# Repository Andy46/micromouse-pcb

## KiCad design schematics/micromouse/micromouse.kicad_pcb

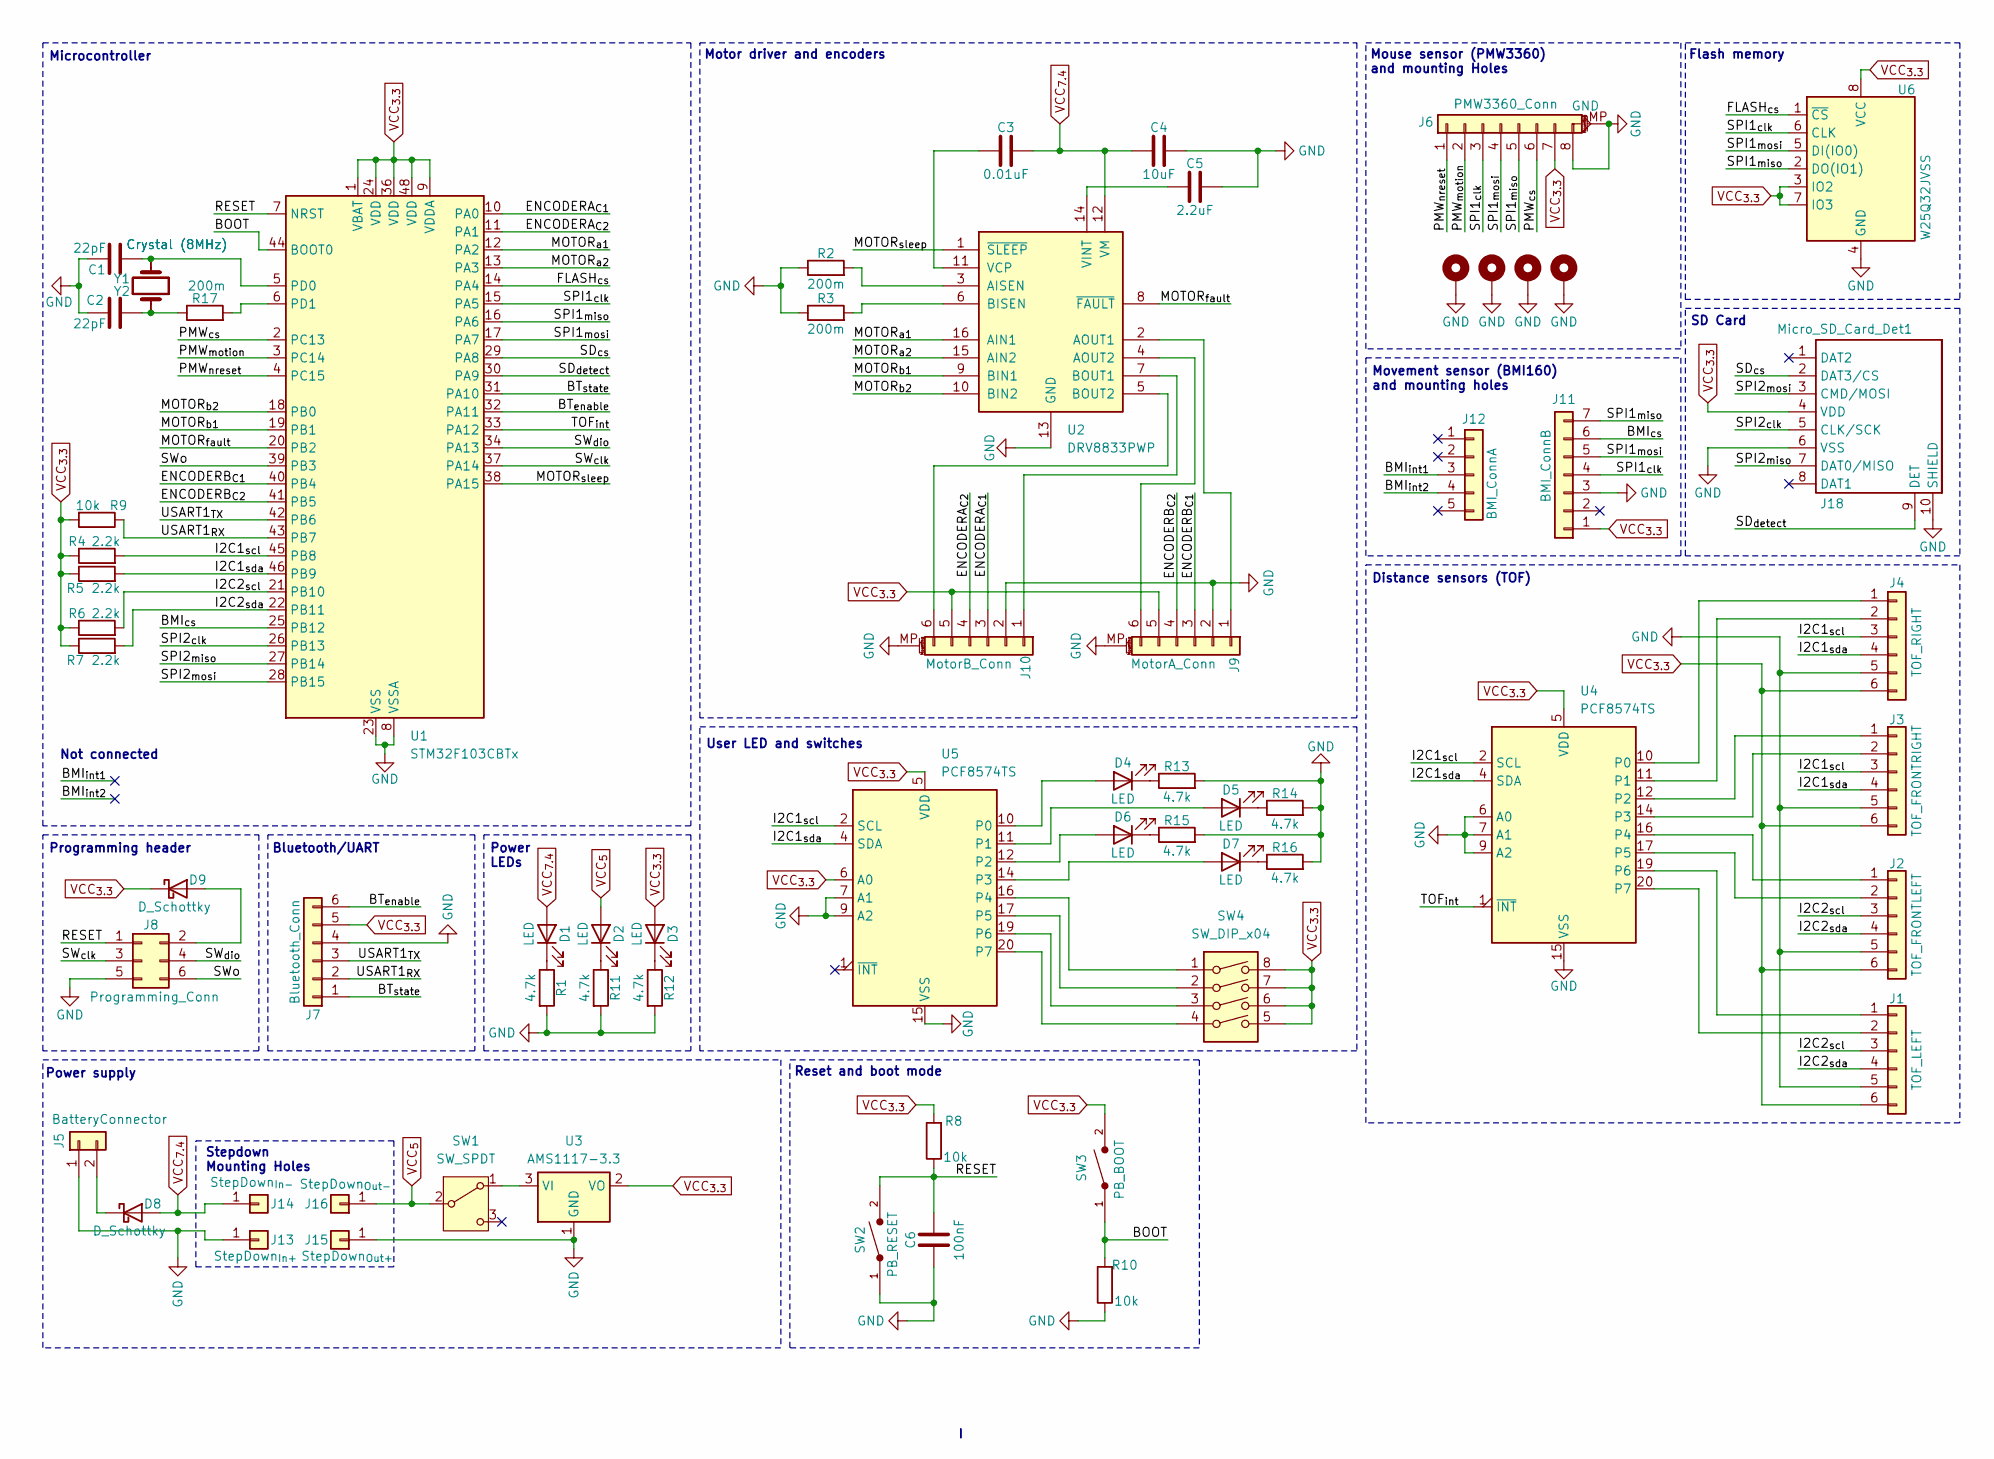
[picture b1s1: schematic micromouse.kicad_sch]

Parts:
C1, C2: 22pF; C_0805_2012Metric_Pad1.18x1.45mm_HandSolder
C3: 0.01uF; C_0805_2012Metric_Pad1.18x1.45mm_HandSolder
C4: 10uF; C_0805_2012Metric_Pad1.18x1.45mm_HandSolder
C5: 2.2uF; C_0805_2012Metric_Pad1.18x1.45mm_HandSolder
C6: 100nF; C_0805_2012Metric_Pad1.18x1.45mm_HandSolder
D1, D2, D3, D4, D5, D6, D7: LED; LED_0805_2012Metric_Pad1.15x1.40mm_HandSolder
D8, D9: D_Schottky; D_SOD-123
H1, H2, H3, H4: MountingHole_Pad; MountingHole_2.2mm_M2_ISO14580_Pad
J1: TOF_LEFT; PinHeader_1x06_P2.54mm_Vertical
J2: TOF_FRONTLEFT; PinHeader_1x06_P2.54mm_Vertical
J3: TOF_FRONTRIGHT; PinHeader_1x06_P2.54mm_Vertical
J4: TOF_RIGHT; PinHeader_1x06_P2.54mm_Vertical
J5: BatteryConnector; JST_XH_B2B-XH-A_1x02_P2.50mm_Vertical
J6: PMW3360_Conn; JST_SH_BM08B-SRSS-TB_1x08-1MP_P1.00mm_Vertical
J7: Bluetooth_Conn; PinHeader_1x06_P2.54mm_Vertical
J8: Programming_Conn; PinHeader_2x03_P2.54mm_Vertical
J9: MotorA_Conn; JST_SH_BM06B-SRSS-TB_1x06-1MP_P1.00mm_Vertical
J10: MotorB_Conn; JST_SH_BM06B-SRSS-TB_1x06-1MP_P1.00mm_Vertical
J11: BMI_ConnB; PinHeader_1x07_P2.54mm_Vertical
J12: BMI_ConnA; PinHeader_1x05_P2.54mm_Vertical
J13: StepDown_{In+}; PinHeader_1x01_P2.54mm_Vertical
J14: StepDown_{In-}; PinHeader_1x01_P2.54mm_Vertical
J15: StepDown_{Out+}; PinHeader_1x01_P2.54mm_Vertical
J16: StepDown_{Out-}; PinHeader_1x01_P2.54mm_Vertical
J18: Micro_SD_Card_Det1; microSD_HC_Hirose_DM3D-SF
R1, R11, R12, R13, R14, R15, R16: 4.7k; R_0805_2012Metric_Pad1.20x1.40mm_HandSolder
R2, R3, R17: 200m; R_0805_2012Metric_Pad1.20x1.40mm_HandSolder
R4, R5, R6, R7: 2.2k; R_0805_2012Metric_Pad1.20x1.40mm_HandSolder
R8, R9, R10: 10k; R_0805_2012Metric_Pad1.20x1.40mm_HandSolder
SW1: SW_SPDT; SW_SPDT_PCM12
SW2: PB_RESET; TE_FSMSM; PARTREV C2
SW3: PB_BOOT; TE_FSMSM; PARTREV C2
SW4: SW_DIP_x04; SW_DIP_SPSTx04_Slide_9.78x12.34mm_W7.62mm_P2.54mm
U1: STM32F103CBTx; LQFP-48_7x7mm_P0.5mm
U2: DRV8833PWP; HTSSOP-16-1EP_4.4x5mm_P0.65mm_EP3.4x5mm_Mask2.46x2.31mm_The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
U3: AMS1117-3.3; SOT-223-3_TabPin2
U4, U5: PCF8574TS; SSOP-20_4.4x6.5mm_P0.65mm
U6: W25Q32JVSS; SOIC-8_5.23x5.23mm_P1.27mm
Y1: Crystal (8MHz); Crystal_SMD_HC49-SD
Y2: Crystal (8MHz); Crystal_HC49-4H_Vertical

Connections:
/BMI_{cs}: J11.6, U1.25 (PB12)
/BMI_{int1}: J12.3
/BMI_{int2}: J12.4
/BOOT: R10.2, SW3.1, U1.44 (BOOT0)
/BT_{enable}: J7.6, U1.32 (PA11)
/BT_{state}: J7.1, U1.31 (PA10)
/ENCODERA_{C1}: J10.3, U1.10 (PA0)
/ENCODERA_{C2}: J10.4, U1.11 (PA1)
/ENCODERB_{C1}: J9.3, U1.40 (PB4)
/ENCODERB_{C2}: J9.4, U1.41 (PB5)
/FLASH_{cs}: U1.14 (PA4), U6.1 (~CS)
/I2C1_{scl}: J3.3, J4.3, R4.2, U1.45 (PB8), U4.2 (SCL), U5.2 (SCL)
/I2C1_{sda}: J3.4, J4.4, R5.2, U1.46 (PB9), U4.4 (SDA), U5.4 (SDA)
/I2C2_{scl}: J1.3, J2.3, R6.2, U1.21 (PB10)
/I2C2_{sda}: J1.4, J2.4, R7.2, U1.22 (PB11)
/MOTOR_{a1}: U1.12 (PA2), U2.16 (AIN1)
/MOTOR_{a2}: U1.13 (PA3), U2.15 (AIN2)
/MOTOR_{b1}: U1.19 (PB1), U2.9 (BIN1)
/MOTOR_{b2}: U1.18 (PB0), U2.10 (BIN2)
/MOTOR_{fault}: U1.20 (PB2), U2.8 (~FAULT)
/MOTOR_{sleep}: U1.38 (PA15), U2.1 (~SLEEP)
/PMW_{cs}: J6.6, U1.2 (PC13)
/PMW_{motion}: J6.2, U1.3 (PC14)
/PMW_{nreset}: J6.1, U1.4 (PC15)
/RESET: C6.1, J8.1, R8.1, SW2.2, U1.7 (NRST)
/SD_{cs}: J18.2 (DAT3/CS), U1.29 (PA8)
/SD_{detect}: J18.9 (DET), U1.30 (PA9)
/SPI1_{clk}: J6.3, J11.4, U1.15 (PA5), U6.6 (CLK)
/SPI1_{miso}: J6.5, J11.7, U1.16 (PA6), U6.2 (DO(IO1))
/SPI1_{mosi}: J6.4, J11.5, U1.17 (PA7), U6.5 (DI(IO0))
/SPI2_{clk}: J18.5 (CLK/SCK), U1.26 (PB13)
/SPI2_{miso}: J18.7 (DAT0/MISO), U1.27 (PB14)
/SPI2_{mosi}: J18.3 (CMD/MOSI), U1.28 (PB15)
/SW_{clk}: J8.3, U1.37 (PA14)
/SW_{dio}: J8.4, U1.34 (PA13)
/SWo: J8.6, U1.39 (PB3)
/TOF_{int}: U1.33 (PA12), U4.1 (~INT)
/USART1_{RX}: J7.2, R9.1, U1.43 (PB7)
/USART1_{TX}: J7.3, U1.42 (PB6)
GND: C1.1, C2.2, C4.2, C5.2, C6.2, H1.1, H2.1, H3.1, H4.1, J1.5, J2.5, J3.5, J4.5, J5.1, J6.8, J6.MP (MountPin), J7.4, J8.5, J9.2, J9.MP (MountPin), J10.2, J10.MP (MountPin), J11.3, J13.1, J15.1, J18.6 (VSS), J18.10 (SHIELD), R1.2, R2.1, R3.1, R10.1, R11.2, R12.2, R13.2, R14.2, R15.2, R16.2, SW2.1, U1.8 (VSSA), U1.23 (VSS), U1.35 (VSS), U1.47 (VSS), U2.13 (GND), U2.17 (GND), U3.1 (GND), U4.6 (A0), U4.7 (A1), U4.9 (A2), U4.15 (VSS), U5.7 (A1), U5.9 (A2), U5.15 (VSS), U6.4 (GND)
unnamed: C2.1, R17.1, Y1.1, Y2.1
unnamed: D1.1 (K), R1.1
unnamed: D2.1 (K), R11.1
unnamed: D3.1 (K), R12.1
unnamed: D4.2 (A), U5.10 (P0)
unnamed: D4.1 (K), R13.1
unnamed: D5.2 (A), U5.11 (P1)
unnamed: D5.1 (K), R14.1
unnamed: D6.2 (A), U5.12 (P2)
unnamed: D6.1 (K), R15.1
unnamed: D7.2 (A), U5.14 (P3)
unnamed: D7.1 (K), R16.1
unnamed: D8.1 (K), J5.2
unnamed: D9.2 (A), J8.2
unnamed: J1.1, U4.19 (P6)
unnamed: J1.2, U4.20 (P7)
unnamed: J2.1, U4.16 (P4)
unnamed: J2.2, U4.17 (P5)
unnamed: J3.1, U4.12 (P2)
unnamed: J3.2, U4.14 (P3)
unnamed: J4.1, U4.10 (P0)
unnamed: J4.2, U4.11 (P1)
unnamed: J9.1, U2.2 (AOUT1)
unnamed: J9.6, U2.4 (AOUT2)
unnamed: J10.1, U2.7 (BOUT1)
unnamed: J10.6, U2.5 (BOUT2)
unnamed: SW1.1 (A), U3.3 (VI)
unnamed: C1.2, U1.5 (PD0), Y1.2, Y2.2
unnamed: R17.2, U1.6 (PD1)
unnamed: R2.2, U2.3 (AISEN)
unnamed: R3.2, U2.6 (BISEN)
unnamed: C3.1, U2.11 (VCP)
unnamed: C5.1, U2.14 (VINT)
unnamed: SW4.1, U5.16 (P4)
unnamed: SW4.2, U5.17 (P5)
unnamed: SW4.3, U5.19 (P6)
unnamed: SW4.4, U5.20 (P7)
VCC_{3.3}: D3.2 (A), D9.1 (K), J1.6, J2.6, J3.6, J4.6, J6.7, J7.5, J9.5, J10.5, J11.1, J18.4 (VDD), R4.1, R5.1, R6.1, R7.1, R8.2, R9.2, SW3.2, SW4.5, SW4.6, SW4.7, SW4.8, U1.1 (VBAT), U1.9 (VDDA), U1.24 (VDD), U1.36 (VDD), U1.48 (VDD), U3.2 (VO), U4.5 (VDD), U5.5 (VDD), U5.6 (A0), U6.3 (IO2), U6.7 (IO3), U6.8 (VCC)
VCC_{5}: D2.2 (A), J16.1, SW1.2 (B)
VCC_{7.4}: C3.2, C4.1, D1.2 (A), D8.2 (A), J14.1, U2.12 (VM)

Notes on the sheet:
SD Card
Flash memory
Distance sensors (TOF)
Programming header
Not connected
User LED and switches
Movement sensor (BMI160) and mounting holes
Bluetooth/UART
Reset and boot mode
Microcontroller
Power LEDs
Stepdown Mounting Holes
Motor driver and encoders
Mouse sensor (PMW3360) and mounting Holes
Power supply

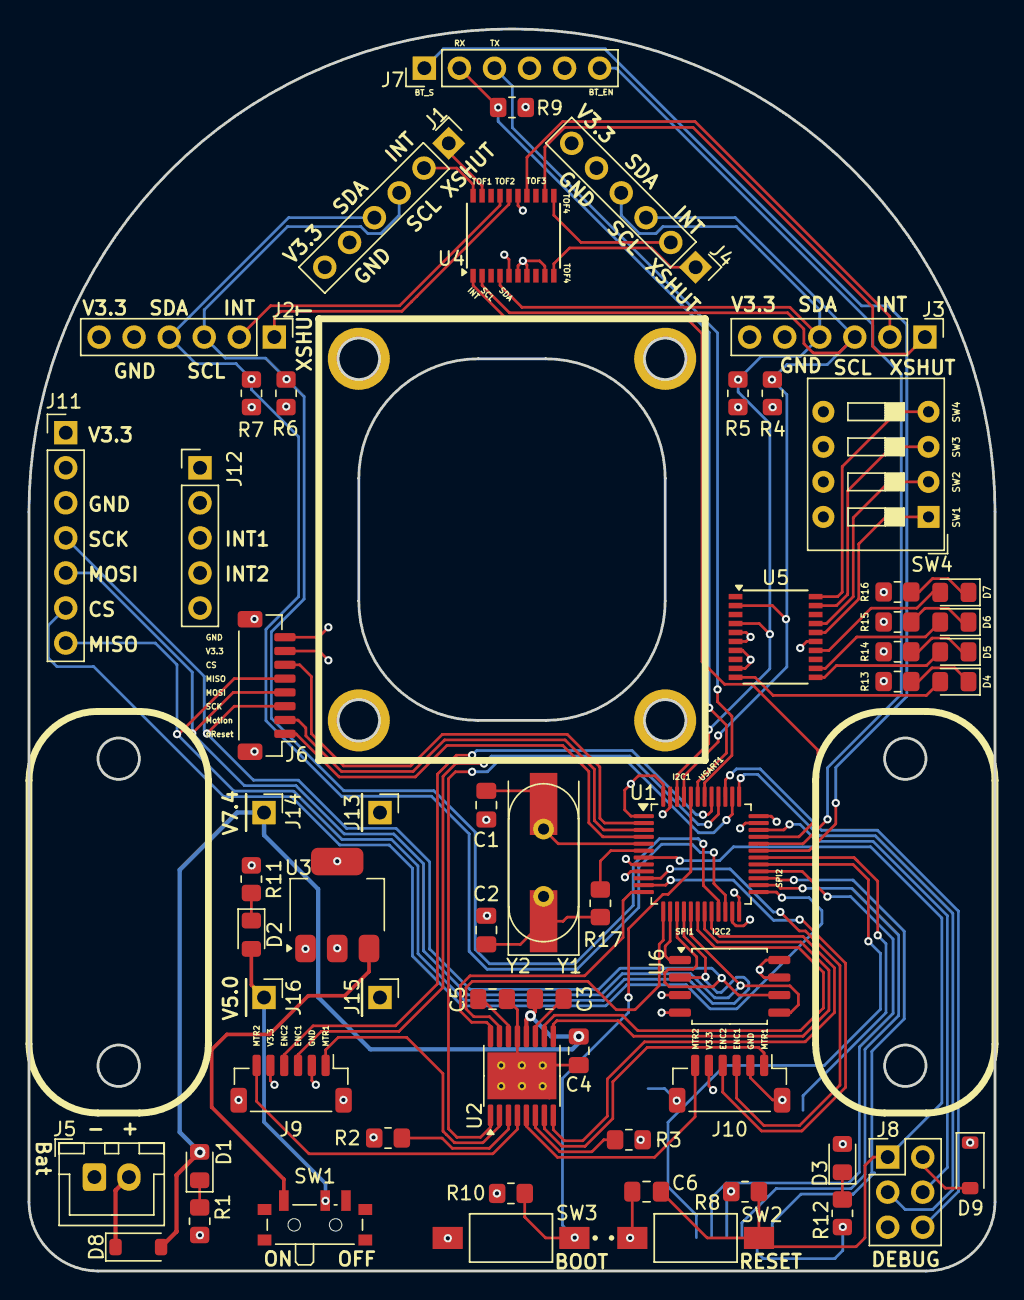
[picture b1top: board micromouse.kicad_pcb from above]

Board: 4 copper layers, 70.0 x 90.0 mm, 65 parts (1 on the bottom side), 78 nets.

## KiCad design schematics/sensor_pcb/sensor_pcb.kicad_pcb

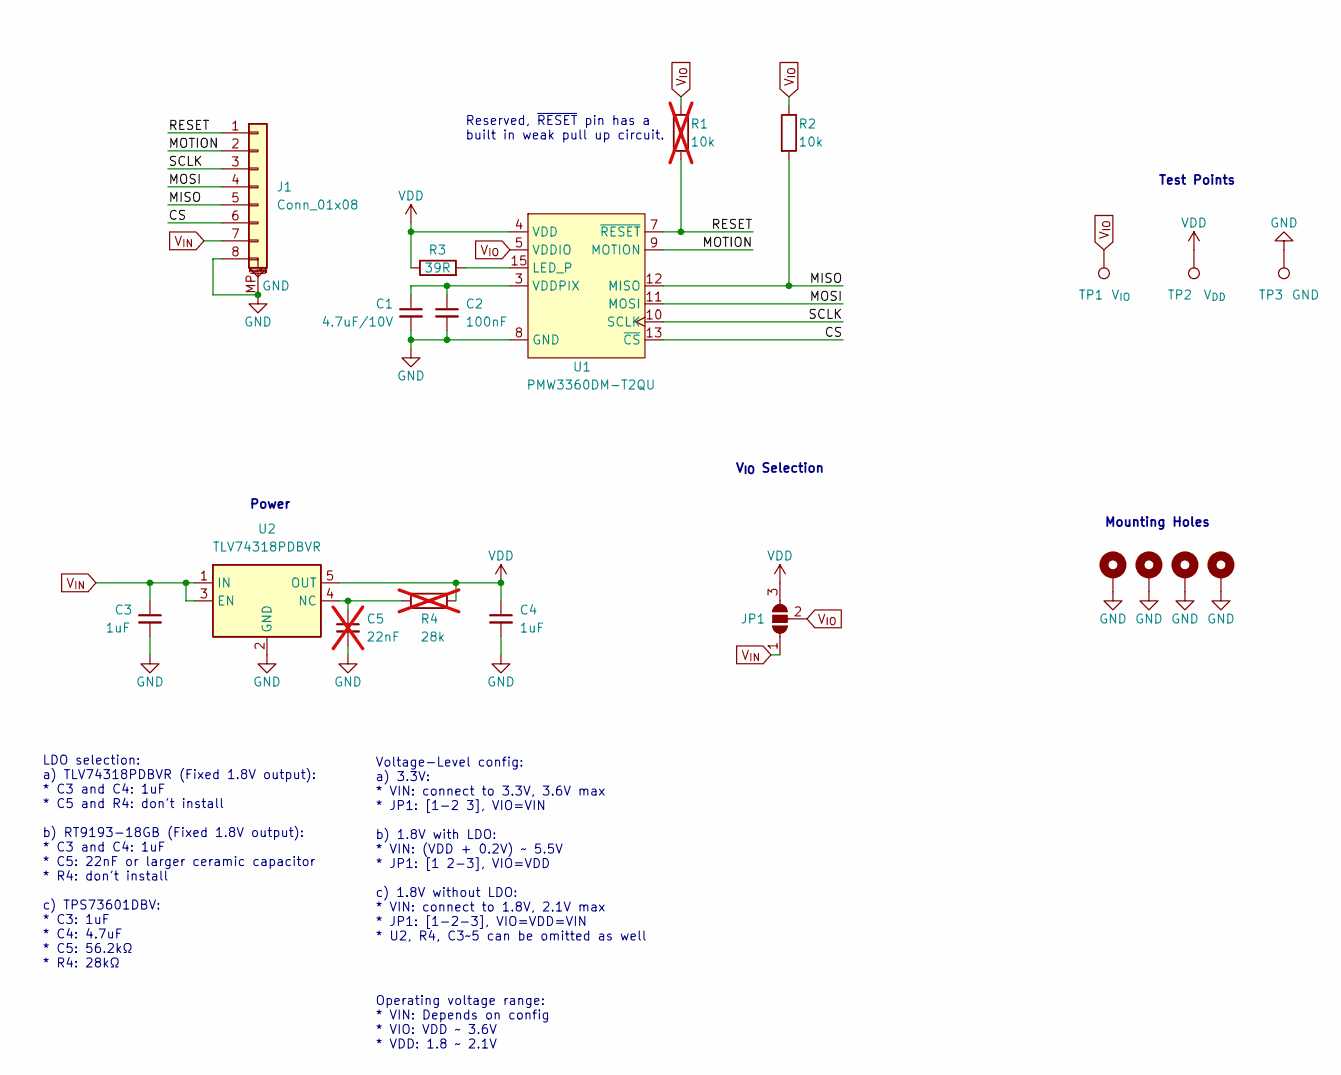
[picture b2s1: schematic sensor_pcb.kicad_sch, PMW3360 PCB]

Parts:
C1: 4.7uF/10V; C_0603_1608Metric_Pad1.08x0.95mm_HandSolder
C2: 100nF; C_0603_1608Metric_Pad1.08x0.95mm_HandSolder
C3, C4: 1uF; C_0603_1608Metric_Pad1.08x0.95mm_HandSolder
C5: 22nF; C_0603_1608Metric_Pad1.08x0.95mm_HandSolder; Mfr. # CL10B223KB8NNNC; LCSC C21122; not fitted
H1, H2, H3, H4: MountingHole_Pad; MountingHole_2.2mm_M2_ISO14580_Pad
J1: Conn_01x08; JST_SH_SM08B-SRSS-TB_1x08-1MP_P1.00mm_Horizontal
JP1: SolderJumper_3_Open; SolderJumper-3_P1.3mm_Open_RoundedPad1.0x1.5mm_NumberLabels
R1: 10k; R_0603_1608Metric_Pad0.98x0.95mm_HandSolder; not fitted
R2: 10k; R_0603_1608Metric_Pad0.98x0.95mm_HandSolder
R3: 39R; R_0603_1608Metric_Pad0.98x0.95mm_HandSolder
R4: 28k; R_0603_1608Metric_Pad0.98x0.95mm_HandSolder; not fitted
TP1: V_{IO}; TestPoint_Pad_D1.0mm
TP2: V_{DD}; TestPoint_Pad_D1.0mm
TP3: GND; TestPoint_Pad_D1.0mm
U1: PMW3360DM-T2QU; PMW3360DM-T2QU 16Pin
U2: TLV74318PDBVR; SOT-23-5; Mfr. # TLV74318PDBVR; LCSC C485152

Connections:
/CS: J1.6, U1.13 (~CS)
/MISO: J1.5, R2.2, U1.12 (MISO)
/MOSI: J1.4, U1.11 (MOSI)
/MOTION: J1.2, U1.9 (MOTION)
/RESET: J1.1, R1.2, U1.7 (~RESET)
/SCLK: J1.3, U1.10 (SCLK)
GND: C1.2, C2.2, C3.2, C4.2, C5.2, H1.1, H2.1, H3.1, H4.1, J1.8, J1.MP (MountPin), TP3.1, U1.8 (GND), U2.2 (GND)
unnamed: R3.2, U1.15 (LED_P)
unnamed: C1.1, C2.1, U1.3 (VDDPIX)
unnamed: C5.1, R4.2, U2.4 (NC)
VDD: C4.1, JP1.3 (B), R3.1, R4.1, TP2.1, U1.4 (VDD), U2.5 (OUT)
V_{IN}: C3.1, J1.7, JP1.1 (A), U2.1 (IN), U2.3 (EN)
V_{IO}: JP1.2 (C), R1.1, R2.1, TP1.1, U1.5 (VDDIO)

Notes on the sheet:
Mounting Holes
Test Points
V_{IO} Selection
LDO selection: a) TLV74318PDBVR (Fixed 1.8V output): * C3 and C4: 1uF * C5 and R4: don't install b) RT9193-18GB (Fixed 1.8V output): * C3 and C4: 1uF * C5: 22nF or larger ceramic capacitor * R4: don't install c) TPS73601DBV: * C3: 1uF * C4: 4.7uF * C5: 56.2kΩ * R4: 28kΩ
Operating voltage range: * VIN: Depends on config * VIO: VDD ~ 3.6V * VDD: 1.8 ~ 2.1V
Power
Reserved, ~{RESET} pin has a built in weak pull up circuit.
Voltage-Level config: a) 3.3V: * VIN: connect to 3.3V, 3.6V max * JP1: [1-2 3], VIO=VIN b) 1.8V with LDO: * VIN: (VDD + 0.2V) ~ 5.5V * JP1: [1 2-3], VIO=VDD c) 1.8V without LDO: * VIN: connect to 1.8V, 2.1V max * JP1: [1-2-3], VIO=VDD=VIN * U2, R4, C3~5 can be omitted as well

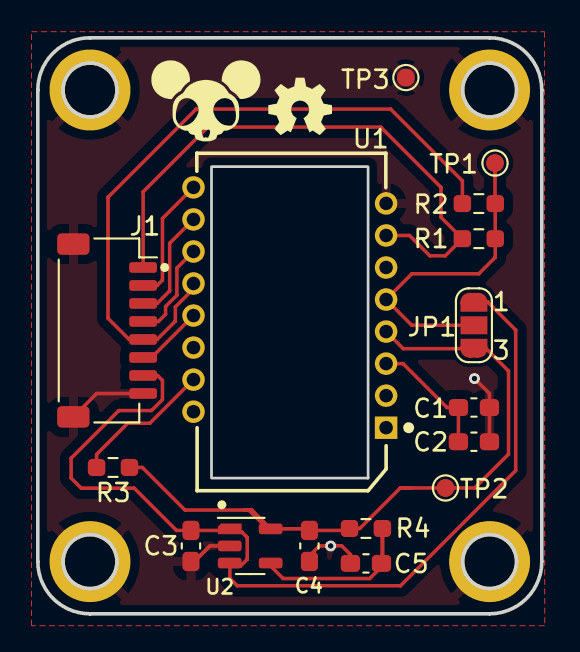
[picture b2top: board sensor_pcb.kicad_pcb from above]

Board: 2 copper layers, 28.0 x 32.0 mm, 20 parts (0 on the bottom side), 13 nets.

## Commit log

2024-06-25 Add base clean schematic
2024-07-20 Add modified pmw3360 sensor pcb to main repository.
2024-07-20 Add datasheets for: * Microcontroller STM32F103C8 * Mouse sensor PMW3360 and Lense LM19 * Voltage regulator TLV743
2024-07-20 Add sensors to kicad library: * BMI270 * PMW3360
2024-07-20 Move datasheets, add application note for smt32f103 hardware development Add PCB cut from 3D model (DXF) Reorganize datasheet, add labels and connectors for tofs i2c (x2), add I2C expancer (PCF8574),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
2024-07-20 Add datasheet for motors driver
2024-07-20 Reorganize again... add things
2024-07-20 Add datasheet for crystal HC-49
2024-07-20 Schamatic status update: * STM32 with external clock, DebugPort and communication lines (SPI1, I2C0 and I2C1) * First version of power supply schematic [TODO: Check possible short circuit] * Motor co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
2024-07-20 Schematic organized in boxes
    Schematic status update:
    * STM32 with external clock, DebugPort(*) and communication lines (SPI1, I2C0 and I2C1 and USART1, with pull-up resistors in I2C and USART RX lines) and power lines (VDDs and VSSs)
    * First version of power supply schematic [TODO: Check possible short circuit]
    * Motor controller schematic
    * Mouse sensor connector + mounting holes
    * Bluetooth connector for HC-05/HC-06
2024-07-20 Schematic status: * STM32 with external clock, DebugPort(*) and communication lines (SPI1, I2C1 and I2C2 and USART1, with pull-up resistors in I2C and USART RX lines) and power lines (VDDs and VSSs) 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
    PCB:
    * Reorganized pcb board to use space below motors
    ToDo:
    * Connect signals to the microcontroller in the schematic (sig
2024-07-20 Add second Crystal for second footprint with holes
2024-07-20 Schematic: * Reorganize STM32 pinout due to Software needs/mititations * Add PCB power protection diodes for Battery port and Programming port.
    PCB:
    * Redistribute all lines
    * Avoid Crystal zone with SPI/I2C lines
    * Add text for element's pinouts
    TODO: Add Test Points for signals?
2024-07-20 Schematic/PCB: Add missing resistor for Crystal, based on STM's AN2586 (Getting started with STM32F10xxx hardware development).
2024-07-20 Schematic: * Add microSD card socket
    PCB:
    * Change BOOT and RESET buttons
    * Add and connect microSD card socket
    * Fix some CRC errors
2024-07-20 Solve DRC errors
2024-07-20 Add QR to tag "MousePCB/1.0"
2024-07-20 Ignore zips

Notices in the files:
schematics/sensor_pcb/sensor_pcb.kicad_pcb:
Open Source Hardware, CERN-OHL-P v2
